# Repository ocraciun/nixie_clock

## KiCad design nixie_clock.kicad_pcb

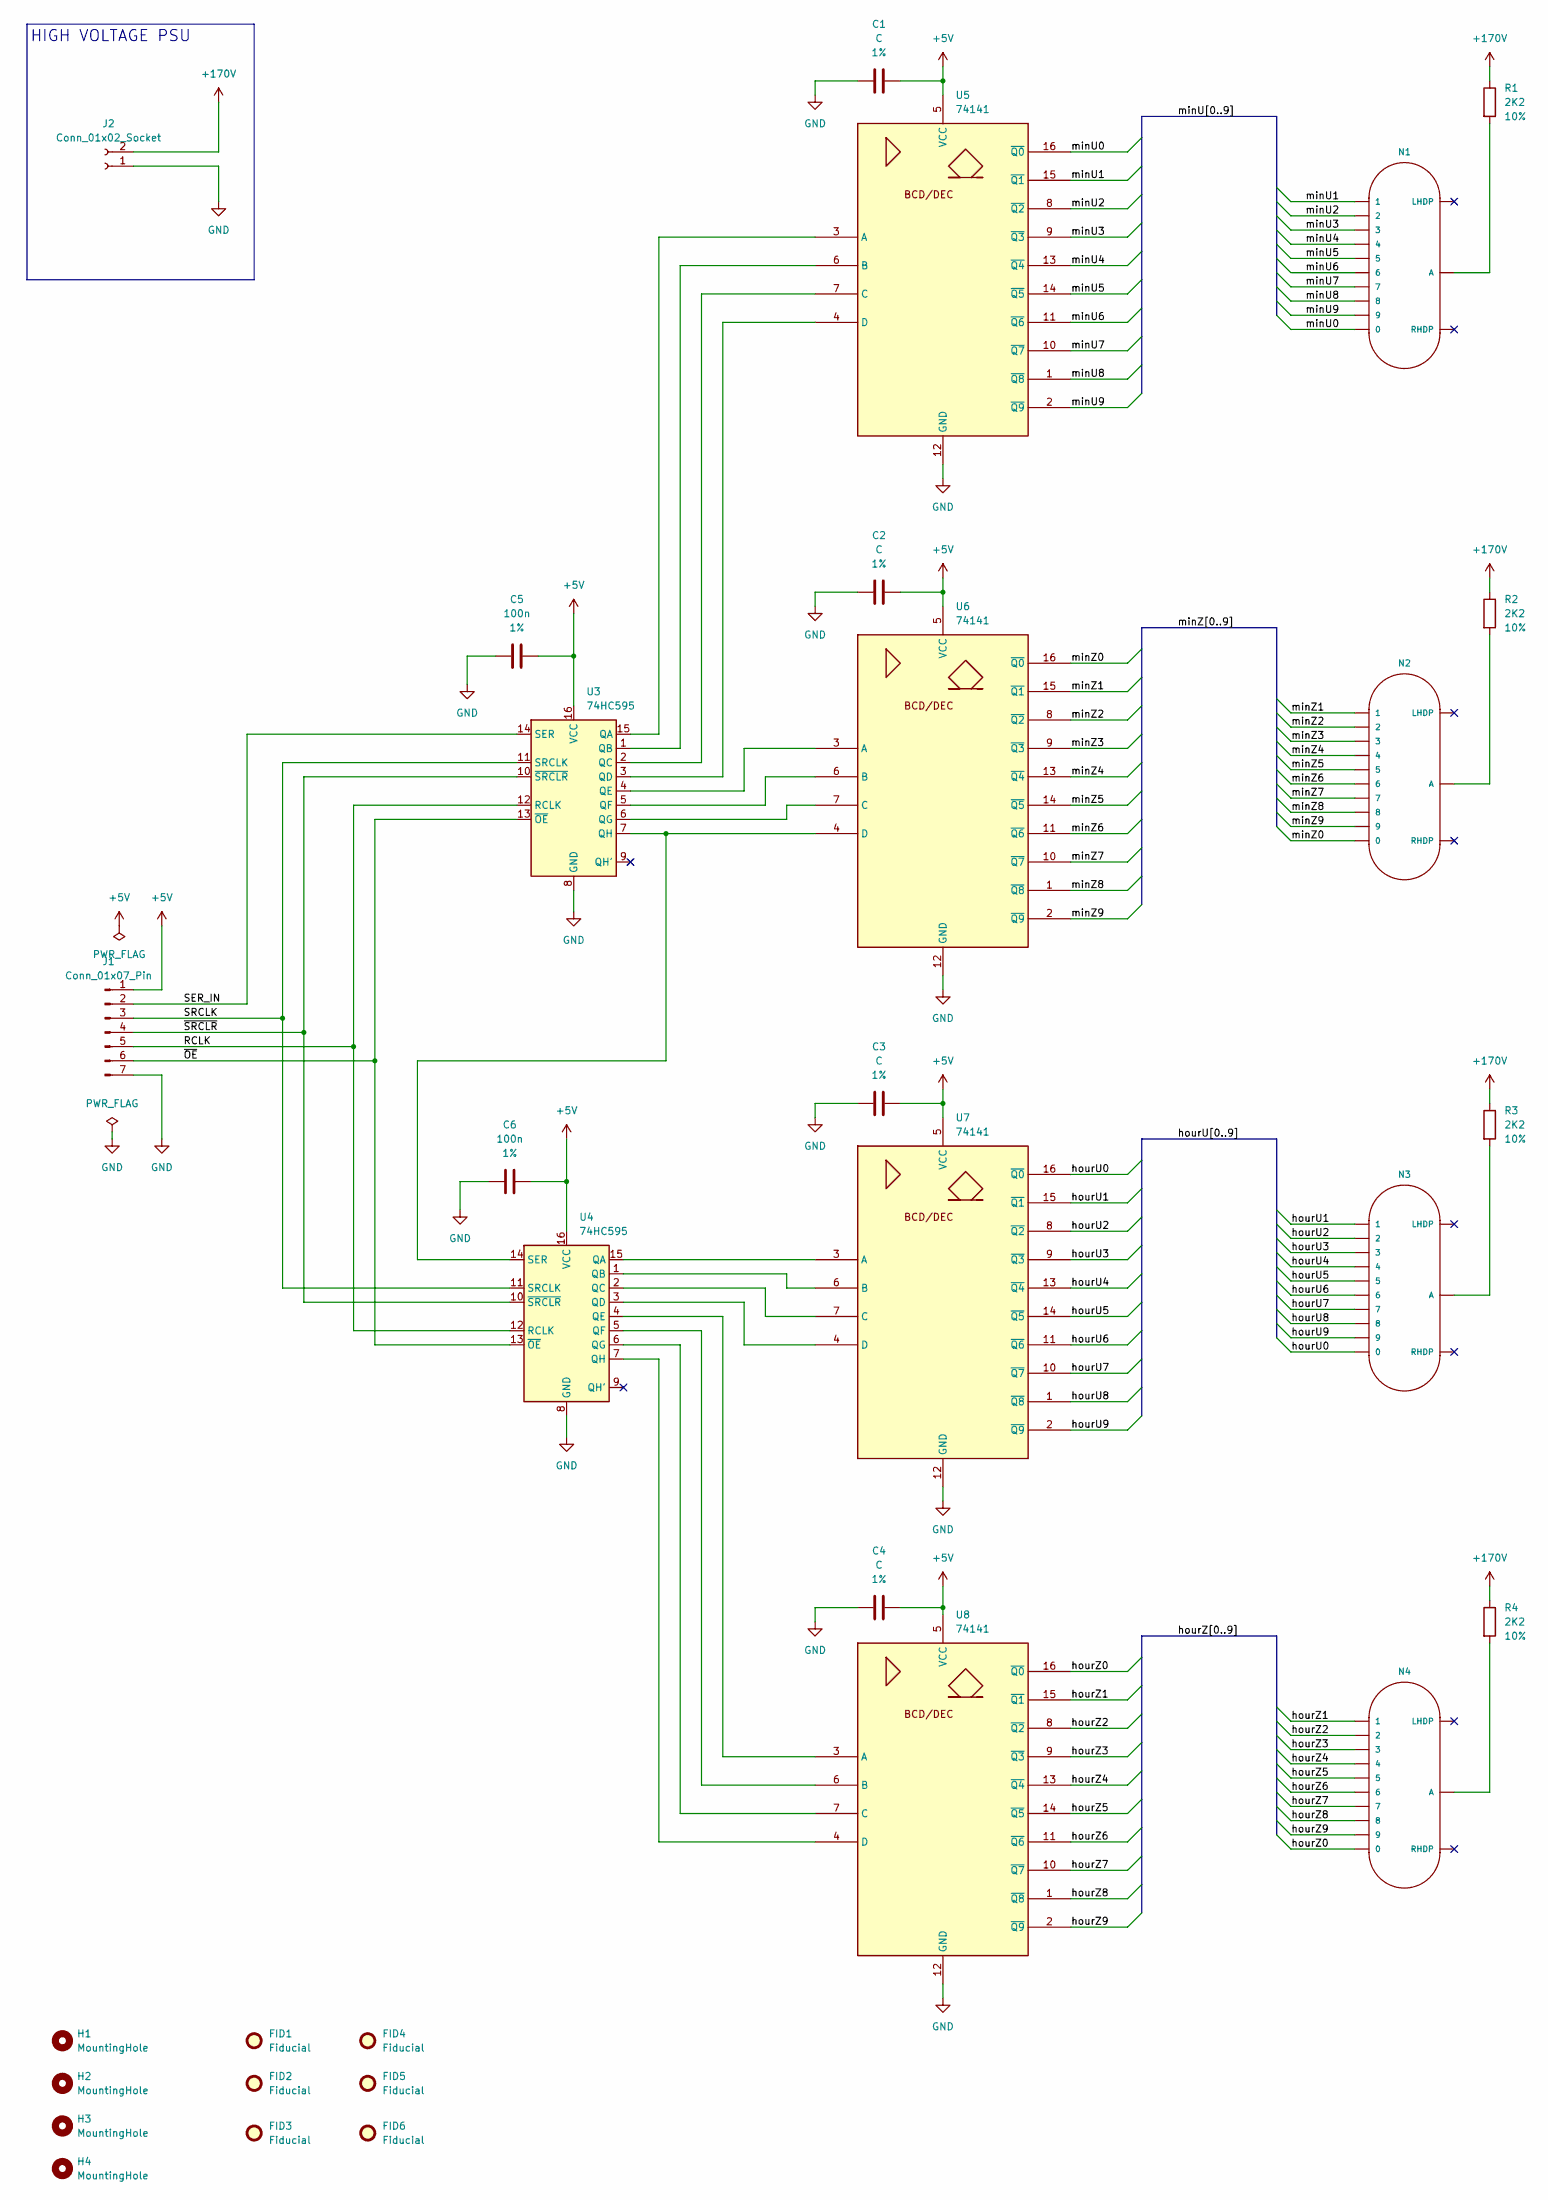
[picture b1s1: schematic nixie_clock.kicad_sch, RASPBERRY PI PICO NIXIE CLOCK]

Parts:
C1, C2, C3, C4: C; C_Disc_D3.0mm_W1.6mm_P2.50mm; Tolerance 1%
C5, C6: 100n; C_Disc_D3.0mm_W1.6mm_P2.50mm; Tolerance 1%
FID1, FID2, FID3, FID4, FID5, FID6: Fiducial; Fiducial_0.5mm_Mask1.5mm
H1, H2, H3, H4: MountingHole; MountingHole_3.2mm_M3
J1: Conn_01x07_Pin; PinHeader_1x07_P2.54mm_Vertical
J2: Conn_01x02_Socket; PinHeader_1x02_P2.54mm_Vertical
N1, N2, N3, N4: IN-14; nixies-us-IN-14
R1, R2, R3, R4: 2K2; R_Axial_DIN0207_L6.3mm_D2.5mm_P10.16mm_Horizontal; Tolerance 10%
U3, U4: 74HC595; DIP-16_W7.62mm_Socket_LongPads
U5, U6, U7, U8: 74141; DIP-16_W7.62mm_Socket_LongPads

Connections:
+5V: C1.2, C2.2, C3.2, C4.2, C5.1, C6.1, J1.1, U3.16 (VCC), U4.16 (VCC), U5.5 (VCC), U6.5 (VCC), U7.5 (VCC), U8.5 (VCC)
+170V: J2.2, R1.1, R2.1, R3.1, R4.1
/RCLK: J1.5, U3.12 (RCLK), U4.12 (RCLK)
/SER_IN: J1.2, U3.14 (SER)
/SRCLK: J1.3, U3.11 (SRCLK), U4.11 (SRCLK)
/hourU0: N3.0, U7.16 (~Q0)
/hourU1: N3.1, U7.15 (~Q1)
/hourU2: N3.2, U7.8 (~Q2)
/hourU3: N3.3, U7.9 (~Q3)
/hourU4: N3.4, U7.13 (~Q4)
/hourU5: N3.5, U7.14 (~Q5)
/hourU6: N3.6, U7.11 (~Q6)
/hourU7: N3.7, U7.10 (~Q7)
/hourU8: N3.8, U7.1 (~Q8)
/hourU9: N3.9, U7.2 (~Q9)
/hourZ0: N4.0, U8.16 (~Q0)
/hourZ1: N4.1, U8.15 (~Q1)
/hourZ2: N4.2, U8.8 (~Q2)
/hourZ3: N4.3, U8.9 (~Q3)
/hourZ4: N4.4, U8.13 (~Q4)
/hourZ5: N4.5, U8.14 (~Q5)
/hourZ6: N4.6, U8.11 (~Q6)
/hourZ7: N4.7, U8.10 (~Q7)
/hourZ8: N4.8, U8.1 (~Q8)
/hourZ9: N4.9, U8.2 (~Q9)
/minU0: N1.0, U5.16 (~Q0)
/minU1: N1.1, U5.15 (~Q1)
/minU2: N1.2, U5.8 (~Q2)
/minU3: N1.3, U5.9 (~Q3)
/minU4: N1.4, U5.13 (~Q4)
/minU5: N1.5, U5.14 (~Q5)
/minU6: N1.6, U5.11 (~Q6)
/minU7: N1.7, U5.10 (~Q7)
/minU8: N1.8, U5.1 (~Q8)
/minU9: N1.9, U5.2 (~Q9)
/minZ0: N2.0, U6.16 (~Q0)
/minZ1: N2.1, U6.15 (~Q1)
/minZ2: N2.2, U6.8 (~Q2)
/minZ3: N2.3, U6.9 (~Q3)
/minZ4: N2.4, U6.13 (~Q4)
/minZ5: N2.5, U6.14 (~Q5)
/minZ6: N2.6, U6.11 (~Q6)
/minZ7: N2.7, U6.10 (~Q7)
/minZ8: N2.8, U6.1 (~Q8)
/minZ9: N2.9, U6.2 (~Q9)
/~OE: J1.6, U3.13 (~OE), U4.13 (~OE)
/~SRCLR: J1.4, U3.10 (~SRCLR), U4.10 (~SRCLR)
GND: C1.1, C2.1, C3.1, C4.1, C5.2, C6.2, J1.7, J2.1, U3.8 (GND), U4.8 (GND), U5.12 (GND), U6.12 (GND), U7.12 (GND), U8.12 (GND)
unnamed: N1.A, R1.2
unnamed: N2.A, R2.2
unnamed: N3.A, R3.2
unnamed: N4.A, R4.2
unnamed: U3.15 (QA), U5.3 (A)
unnamed: U3.1 (QB), U5.6 (B)
unnamed: U3.2 (QC), U5.7 (C)
unnamed: U3.3 (QD), U5.4 (D)
unnamed: U3.4 (QE), U6.3 (A)
unnamed: U3.5 (QF), U6.6 (B)
unnamed: U3.6 (QG), U6.7 (C)
unnamed: U3.7 (QH), U4.14 (SER), U6.4 (D)
unnamed: U4.15 (QA), U7.3 (A)
unnamed: U4.1 (QB), U7.6 (B)
unnamed: U4.2 (QC), U7.7 (C)
unnamed: U4.3 (QD), U7.4 (D)
unnamed: U4.4 (QE), U8.3 (A)
unnamed: U4.5 (QF), U8.6 (B)
unnamed: U4.6 (QG), U8.7 (C)
unnamed: U4.7 (QH), U8.4 (D)

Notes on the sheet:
HIGH VOLTAGE PSU

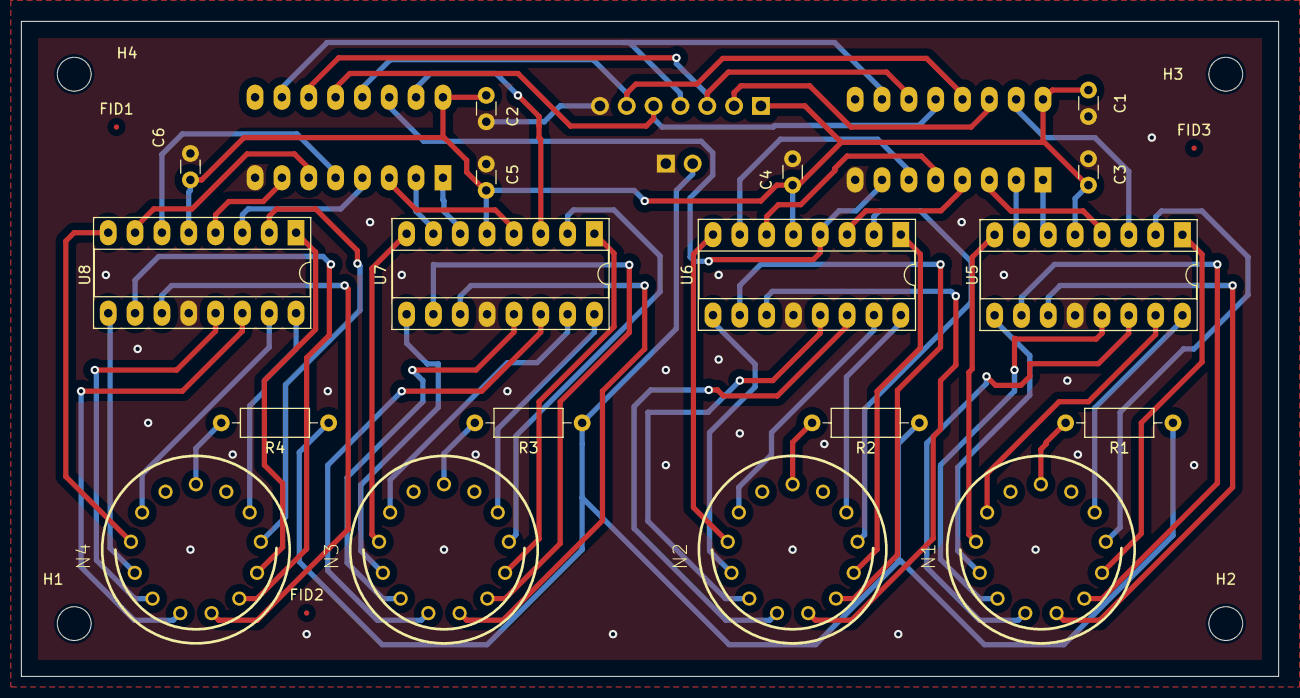
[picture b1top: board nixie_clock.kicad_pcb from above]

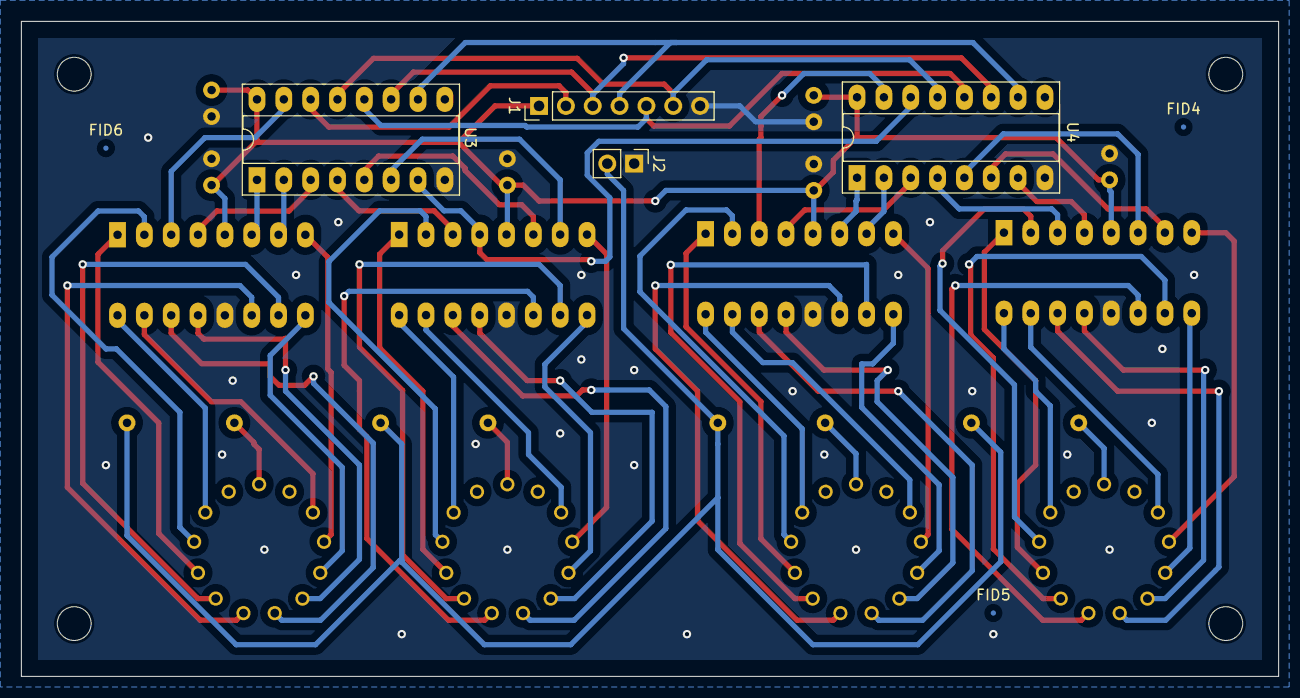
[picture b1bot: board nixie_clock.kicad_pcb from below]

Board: 2 copper layers, 119.0 x 62.0 mm, 32 parts (7 on the bottom side), 68 nets.

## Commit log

2024-07-28 Add first version of nixie clock
2024-07-28 Add schematic as pdf
